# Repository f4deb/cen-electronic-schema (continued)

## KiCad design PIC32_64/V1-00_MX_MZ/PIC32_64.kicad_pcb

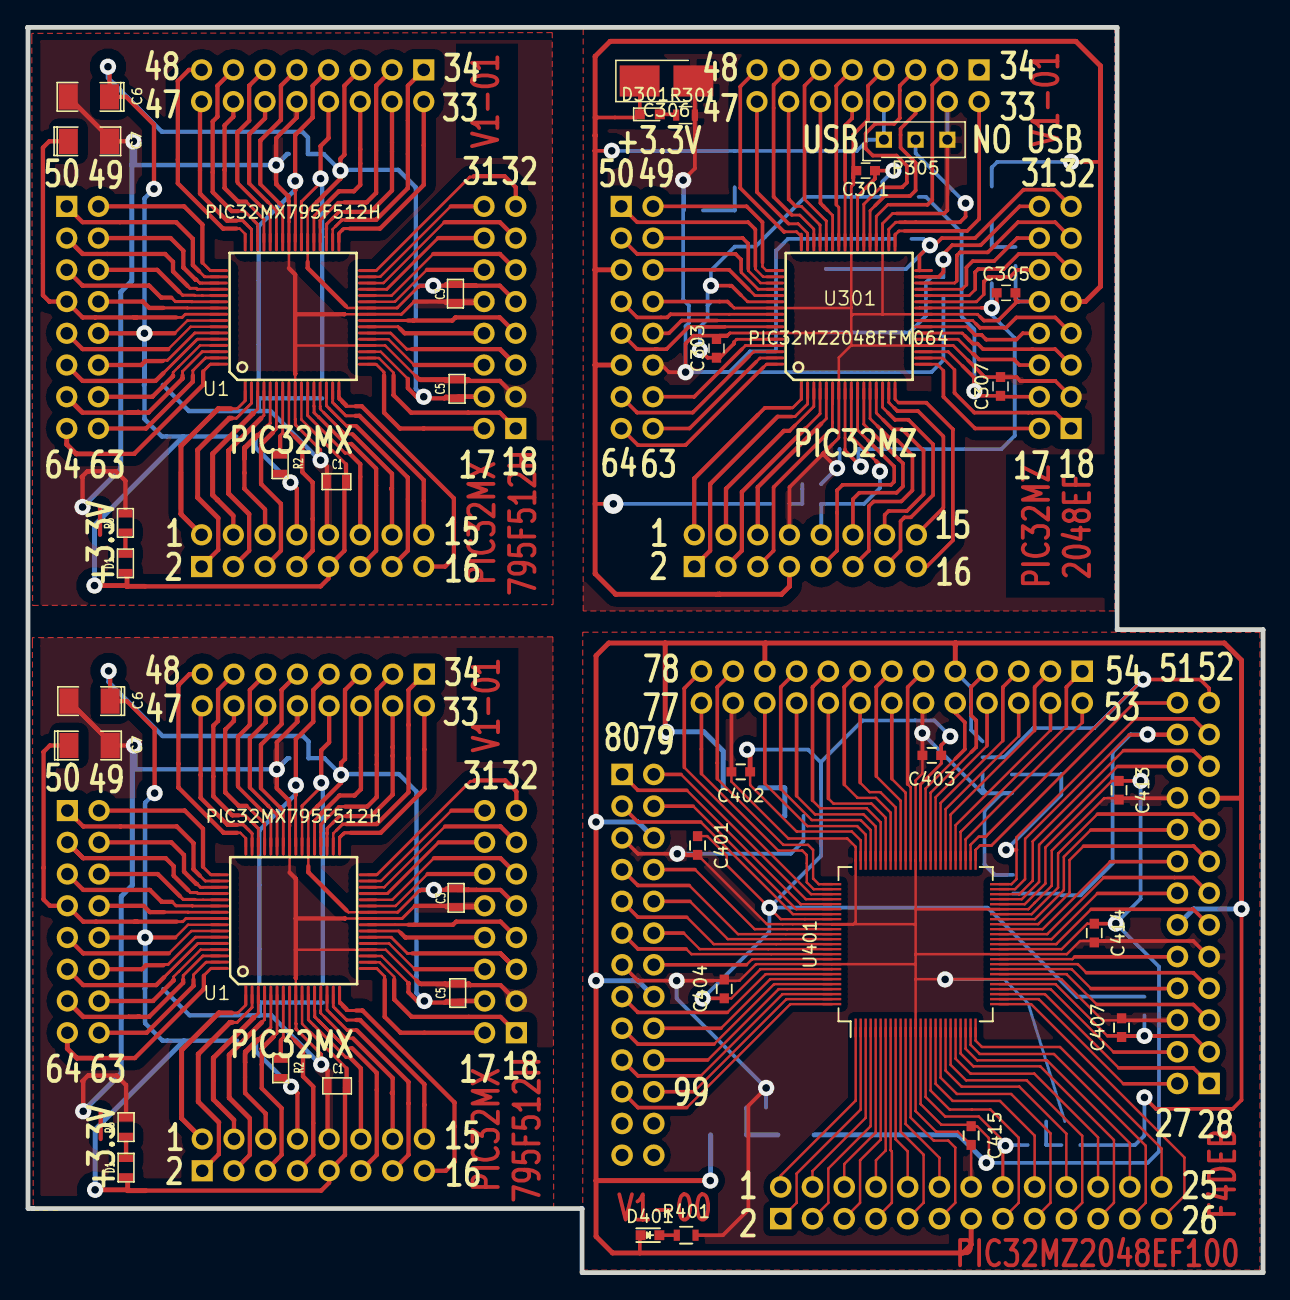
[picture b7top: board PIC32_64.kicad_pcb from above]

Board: 2 copper layers, 98.9 x 99.7 mm, 97 parts (0 on the bottom side), 213 nets.

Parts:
C1, C1#2, C2, C2#2, C3, C3#2, C4, C4#2, C5, C5#2, C8, C8#2, C9, C9#2: 100n; SM0603_Capa
C6, C6#2, C7, C7#2: 10u/10V; SM1206POL
C301, C302, C303, C304, C305, C307, C310, C401, C402, C403, C404, C407, C411, C413, C414, C415: 100n; C_0603
C306: 10u/10V; CP_Tantalum_Case-B_EIA-3528-21_Hand
C308, C309, C408, C409: 10n; C_0603
C311, C312, C410, C412: 22p; C_0603
D1, D1#2: LED; SM0603
D301, D401: LED; LED_0603
L301, L302, L303, L304, L401, L402, L403, L404: Ferrite_Bead_Small; R_1206
P1, P1#2, P2, P2#2, P3, P3#2, P4, P4#2, P301, P302, P303, P304: CONN_8X2; Socket_Strip_Straight_2x08_Pitch2.54mm
P305: CAVALIER2; SL-103-X-XX_1x03
P401, P402, P404, P405: CONN_13X2; Socket_Strip_Straight_2x13
P403: CAVALIER2; GS3
R1, R1#2: 10k; SM0603_Resistor
R2, R2#2: 470; SM0603_Resistor
R3, R3#2: 1k; SM0603_Resistor
R4, R4#2: 0; SM0603_Resistor
R301, R303, R401, R403: 1k; R_0603
R302: 0; R_1206
R304, R404: 10k; R_0603
R402: 0; R_0603
U1, U1#2: PIC32MX795F512H; TQFP_64
U301: PIC32MZ2048EFM064; TQFP_64
U401: PIC32MZ2048EF100; TQFP-100_12x12mm_Pitch0.4mm
X1, X1#2: 8Mhz; QTZ
X301: 24Mhz; QTZ
X401: 24Mhz; Crystal_HC49-SD_SMD

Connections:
+3.3V: C1.1, C1#2.1, C2.1, C2#2.1, C3.1, C3#2.1, C4.1, C4#2.1, C6.1, C6#2.1, D1.1, D1#2.1, P1.9, P1#2.9, P2.5, P2#2.5, P3.9, P3#2.9, P4.10, P4#2.10, R1.2, R1#2.2, R4.1, R4#2.1, U1.10, U1.26, U1.38, U1.57, U1#2.10, U1#2.26, U1#2.38, U1#2.57
+3.3VA: D401.1, L401.1, L403.1, P401.13, P402.12, P402.19, P403.1, P404.9, P404.21, P405.6, P405.16, R404.2
+3.3VP: C306.1, D301.1, L301.1, L303.1, P301.7, P302.9, P303.8, P304.5, P304.11, P305.1, R304.2
/1: P1.2, P1#2.2, U1.1, U1#2.1
/2: P1.1, P1#2.1, U1.2, U1#2.2
/3: P1.4, P1#2.4, U1.3, U1#2.3
/4: P1.3, P1#2.3, U1.4, U1#2.4
/5: P1.6, P1#2.6, U1.5, U1#2.5
/6: P1.5, P1#2.5, U1.6, U1#2.6
/7: P1.8, P1#2.8, R1.1, R1#2.1, R2.2, R2#2.2
/8: P1.7, P1#2.7, U1.8, U1#2.8
/11: P1.12, P1#2.12, U1.11, U1#2.11
/12: P1.11, P1#2.11, U1.12, U1#2.12
/13: P1.14, P1#2.14, U1.13, U1#2.13
/14: P1.13, P1#2.13, U1.14, U1#2.14
/15: P1.16, P1#2.16, U1.15, U1#2.15
/16: P1.15, P1#2.15, U1.16, U1#2.16
/17: P3.2, P3#2.2, U1.17, U1#2.17
/18: P3.1, P3#2.1, U1.18, U1#2.18
/19: C5.1, C5#2.1, P3.4, P3#2.4, R4.2, R4#2.2, U1.19, U1#2.19
/21: P3.6, P3#2.6, U1.21, U1#2.21
/22: P3.5, P3#2.5, U1.22, U1#2.22
/23: P3.8, P3#2.8, U1.23, U1#2.23
/24: P3.7, P3#2.7, U1.24, U1#2.24
/27: P3.12, P3#2.12, U1.27, U1#2.27
/28: P3.11, P3#2.11, U1.28, U1#2.28
/29: P3.14, P3#2.14, U1.29, U1#2.29
/30: P3.13, P3#2.13, U1.30, U1#2.30
/31: P3.16, P3#2.16, U1.31, U1#2.31
/32: P3.15, P3#2.15, U1.32, U1#2.32
/33: P2.2, P2#2.2, U1.33, U1#2.33
/34: P2.1, P2#2.1, U1.34, U1#2.34
/35: P2.4, P2#2.4, U1.35, U1#2.35
/36: P2.3, P2#2.3, U1.36, U1#2.36
/37: P2.6, P2#2.6, U1.37, U1#2.37
/39: C8.1, C8#2.1, P2.8, P2#2.8, U1.39, U1#2.39, X1.2, X1#2.2
/40: C9.1, C9#2.1, P2.7, P2#2.7, U1.40, U1#2.40, X1.1, X1#2.1
/42: P2.9, P2#2.9, U1.42, U1#2.42
/43: P2.12, P2#2.12, U1.43, U1#2.43
/44: P2.11, P2#2.11, U1.44, U1#2.44
/45: P2.14, P2#2.14, U1.45, U1#2.45
/46: P2.13, P2#2.13, U1.46, U1#2.46
/47: P2.16, P2#2.16, U1.47, U1#2.47
/48: P2.15, P2#2.15, U1.48, U1#2.48
/49: P4.2, P4#2.2, U1.49, U1#2.49
/50: P4.1, P4#2.1, U1.50, U1#2.50
/51: P4.4, P4#2.4, U1.51, U1#2.51
/52: P4.3, P4#2.3, U1.52, U1#2.52
/53: P4.6, P4#2.6, U1.53, U1#2.53
/54: P4.5, P4#2.5, U1.54, U1#2.54
/55: P4.8, P4#2.8, U1.55, U1#2.55
/56: C7.1, C7#2.1, P4.7, P4#2.7, U1.56, U1#2.56
/58: P4.9, P4#2.9, U1.58, U1#2.58
/59: P4.12, P4#2.12, U1.59, U1#2.59
/60: P4.11, P4#2.11, U1.60, U1#2.60
/61: P4.14, P4#2.14, U1.61, U1#2.61
/62: P4.13, P4#2.13, U1.62, U1#2.62
/63: P4.16, P4#2.16, U1.63, U1#2.63
/64: P4.15, P4#2.15, U1.64, U1#2.64
/PIC32MZ2048EF100/1: P401.2, U401.1
/PIC32MZ2048EF100/2: P401.1, U401.2
/PIC32MZ2048EF100/3: P401.4, U401.3
/PIC32MZ2048EF100/4: P401.3, U401.4
/PIC32MZ2048EF100/5: P401.6, U401.5
/PIC32MZ2048EF100/6: P401.5, U401.6
/PIC32MZ2048EF100/7: P401.8, U401.7
/PIC32MZ2048EF100/8: P401.7, U401.8
/PIC32MZ2048EF100/9: P401.10, U401.9
/PIC32MZ2048EF100/10: P401.9, U401.10
/PIC32MZ2048EF100/11: P401.12, U401.11
/PIC32MZ2048EF100/12: P401.11, U401.12
/PIC32MZ2048EF100/15: P401.16, R403.1, U401.15
/PIC32MZ2048EF100/16: P401.15, U401.16
/PIC32MZ2048EF100/17: P401.18, U401.17
/PIC32MZ2048EF100/18: P401.17, U401.18
/PIC32MZ2048EF100/19: P401.20, U401.19
/PIC32MZ2048EF100/20: P401.19, U401.20
/PIC32MZ2048EF100/21: P401.22, U401.21
/PIC32MZ2048EF100/22: P401.21, U401.22
/PIC32MZ2048EF100/23: P401.24, U401.23
/PIC32MZ2048EF100/24: P401.23, U401.24
/PIC32MZ2048EF100/25: P401.26, U401.25
/PIC32MZ2048EF100/26: P401.25, U401.26
/PIC32MZ2048EF100/27: P402.2, U401.27
/PIC32MZ2048EF100/28: P402.1, U401.28
/PIC32MZ2048EF100/29: P402.4, U401.29
/PIC32MZ2048EF100/30: C407.1, P402.3, R402.2, U401.30
/PIC32MZ2048EF100/32: P402.5, U401.32
/PIC32MZ2048EF100/33: P402.8, U401.33
/PIC32MZ2048EF100/34: P402.7, U401.34
/PIC32MZ2048EF100/35: P402.10, U401.35
/PIC32MZ2048EF100/38: P402.11, U401.38
/PIC32MZ2048EF100/39: P402.14, U401.39
/PIC32MZ2048EF100/40: P402.13, U401.40
/PIC32MZ2048EF100/41: P402.16, U401.41
/PIC32MZ2048EF100/42: P402.15, U401.42
/PIC32MZ2048EF100/43: P402.18, U401.43
/PIC32MZ2048EF100/44: P402.17, U401.44
/PIC32MZ2048EF100/47: P402.22, U401.47
/PIC32MZ2048EF100/48: P402.21, U401.48
/PIC32MZ2048EF100/49: C410.1, P402.24, U401.49, X401.2
/PIC32MZ2048EF100/50: C412.1, P402.23, U401.50, X401.1
/PIC32MZ2048EF100/51: P402.26, U401.51
/PIC32MZ2048EF100/52: P402.25, P403.2, U401.52
/PIC32MZ2048EF100/53: P404.2, U401.53
/PIC32MZ2048EF100/54: P404.1, U401.54
/PIC32MZ2048EF100/55: P404.4, U401.55
/PIC32MZ2048EF100/56: P404.3, U401.56
/PIC32MZ2048EF100/57: P404.6, U401.57
/PIC32MZ2048EF100/58: P404.5, U401.58
/PIC32MZ2048EF100/59: P404.8, U401.59
/PIC32MZ2048EF100/60: P404.7, U401.60
/PIC32MZ2048EF100/61: P404.10, U401.61
/PIC32MZ2048EF100/64: P404.11, U401.64
/PIC32MZ2048EF100/65: P404.14, U401.65
/PIC32MZ2048EF100/66: P404.13, U401.66
/PIC32MZ2048EF100/67: P404.16, U401.67
/PIC32MZ2048EF100/68: P404.15, U401.68
/PIC32MZ2048EF100/69: P404.18, U401.69
/PIC32MZ2048EF100/70: P404.17, U401.70
/PIC32MZ2048EF100/71: P404.20, U401.71
/PIC32MZ2048EF100/72: P404.19, U401.72
/PIC32MZ2048EF100/73: P404.22, U401.73
/PIC32MZ2048EF100/76: P404.23, U401.76
/PIC32MZ2048EF100/77: P404.26, U401.77
/PIC32MZ2048EF100/78: P404.25, U401.78
/PIC32MZ2048EF100/79: P405.2, U401.79
/PIC32MZ2048EF100/80: P405.1, U401.80
/PIC32MZ2048EF100/81: P405.4, U401.81
/PIC32MZ2048EF100/82: P405.3, U401.82
/PIC32MZ2048EF100/85: P405.8, U401.85
/PIC32MZ2048EF100/86: P405.7, U401.86
/PIC32MZ2048EF100/87: P405.10, U401.87
/PIC32MZ2048EF100/88: P405.9, U401.88
/PIC32MZ2048EF100/89: P405.12, U401.89
/PIC32MZ2048EF100/90: P405.11, U401.90
/PIC32MZ2048EF100/91: P405.14, U401.91
/PIC32MZ2048EF100/94: P405.15, U401.94
/PIC32MZ2048EF100/95: P405.18, U401.95
/PIC32MZ2048EF100/96: P405.17, U401.96
/PIC32MZ2048EF100/97: P405.20, U401.97
/PIC32MZ2048EF100/98: P405.19, U401.98
/PIC32MZ2048EF100/99: P405.22, U401.99
/PIC32MZ2048EF100/100: P405.21, U401.100
/PIC32MZ20048EF64/1: P301.2, U301.1
/PIC32MZ20048EF64/2: P301.1, U301.2
/PIC32MZ20048EF64/3: P301.4, U301.3
/PIC32MZ20048EF64/4: P301.3, U301.4
/PIC32MZ20048EF64/5: P301.6, U301.5
/PIC32MZ20048EF64/6: P301.5, U301.6
/PIC32MZ20048EF64/9: P301.10, R303.1, U301.9
/PIC32MZ20048EF64/10: P301.9, U301.10
/PIC32MZ20048EF64/11: P301.12, U301.11
/PIC32MZ20048EF64/12: P301.11, U301.12
/PIC32MZ20048EF64/13: P301.14, U301.13
/PIC32MZ20048EF64/14: P301.13, U301.14
/PIC32MZ20048EF64/15: P301.16, U301.15
/PIC32MZ20048EF64/16: P301.15, U301.16
/PIC32MZ20048EF64/17: P302.2, U301.17
/PIC32MZ20048EF64/18: P302.1, U301.18
/PIC32MZ20048EF64/19: C307.1, P302.4, R302.2, U301.19
/PIC32MZ20048EF64/21: P302.6, U301.21
/PIC32MZ20048EF64/22: P302.5, U301.22
/PIC32MZ20048EF64/23: P302.8, U301.23
/PIC32MZ20048EF64/24: P302.7, U301.24
/PIC32MZ20048EF64/27: P302.12, U301.27
/PIC32MZ20048EF64/28: P302.11, U301.28
/PIC32MZ20048EF64/29: P302.14, U301.29
/PIC32MZ20048EF64/30: P302.13, U301.30
/PIC32MZ20048EF64/31: C312.1, P302.16, U301.31, X301.1
/PIC32MZ20048EF64/32: C311.1, P302.15, U301.32, X301.2
/PIC32MZ20048EF64/33: P303.2, U301.33
/PIC32MZ20048EF64/36: P303.3, U301.36
/PIC32MZ20048EF64/37: P303.6, U301.37
/PIC32MZ20048EF64/38: P303.5, U301.38
/PIC32MZ20048EF64/41: P303.10, U301.41
/PIC32MZ20048EF64/42: P303.9, U301.42
/PIC32MZ20048EF64/43: P303.12, U301.43
/PIC32MZ20048EF64/44: P303.11, U301.44
/PIC32MZ20048EF64/45: P303.14, U301.45
/PIC32MZ20048EF64/46: P303.13, U301.46
/PIC32MZ20048EF64/47: P303.16, U301.47
/PIC32MZ20048EF64/48: P303.15, U301.48
/PIC32MZ20048EF64/49: P304.2, U301.49
/PIC32MZ20048EF64/50: P304.1, U301.50
/PIC32MZ20048EF64/51: P304.4, U301.51
/PIC32MZ20048EF64/52: P304.3, U301.52
/PIC32MZ20048EF64/53: P304.6, U301.53
/PIC32MZ20048EF64/56: P304.7, U301.56
/PIC32MZ20048EF64/57: P304.10, U301.57
/PIC32MZ20048EF64/58: P304.9, U301.58
/PIC32MZ20048EF64/61: P304.14, U301.61
/PIC32MZ20048EF64/62: P304.13, U301.62
/PIC32MZ20048EF64/63: P304.16, U301.63
/PIC32MZ20048EF64/64: P304.15, U301.64
GND: C1.2, C1#2.2, C2.2, C2#2.2, C3.2, C3#2.2, C4.2, C4#2.2, C5.2, C5#2.2, C6.2, C6#2.2, C7.2, C7#2.2, C8.2, C8#2.2, C9.2, C9#2.2, P1.10, P1#2.10, P2.10, P2#2.10, P3.3, P3.10, P3#2.3, P3#2.10, R3.2, R3#2.2, U1.9, U1.20, U1.25, U1.41, U1#2.9, U1#2.20, U1#2.25, U1#2.41
GNDA: C401.2, C402.2, C403.2, C404.2, C407.2, C408.2, C409.2, C410.2, C411.2, C412.2, C413.2, C414.2, C415.2, P401.14, P402.6, P402.9, P402.20, P403.3, P404.12, P404.24, P405.5, P405.13, R401.2, U401.13, U401.31, U401.36, U401.45, U401.63, U401.75, U401.84, U401.92
GNDD: C301.2, C302.2, C303.2, C304.2, C305.2, C306.2, C307.2, C308.2, C309.2, C310.2, C311.2, C312.2, P301.8, P302.3, P302.10, P303.4, P303.7, P304.8, P304.12, P305.3, R301.2, U301.7, U301.20, U301.25, U301.35, U301.40, U301.55, U301.59
unnamed: R2.1, R2#2.1, U1.7, U1#2.7
unnamed: D1.2, D1#2.2, R3.1, R3#2.1
unnamed: C301.1, C302.1, C303.1, L302.2, R302.1, U301.39, U301.54, U301.60
unnamed: C304.1, C305.1, L304.2, U301.8, U301.26
unnamed: C308.1, L301.2, L302.1
unnamed: C309.1, L303.2, L304.1
unnamed: C310.1, R303.2, R304.1
unnamed: C401.1, C402.1, C403.1, C404.1, L402.2, R402.1, U401.62, U401.74, U401.83, U401.93
unnamed: C408.1, L401.2, L402.1
unnamed: C409.1, L403.2, L404.1
unnamed: C411.1, R403.2, R404.1
unnamed: C413.1, C414.1, C415.1, L404.2, U401.14, U401.37, U401.46
unnamed: D301.2, R301.1
unnamed: D401.2, R401.1
unnamed: P305.2, U301.34

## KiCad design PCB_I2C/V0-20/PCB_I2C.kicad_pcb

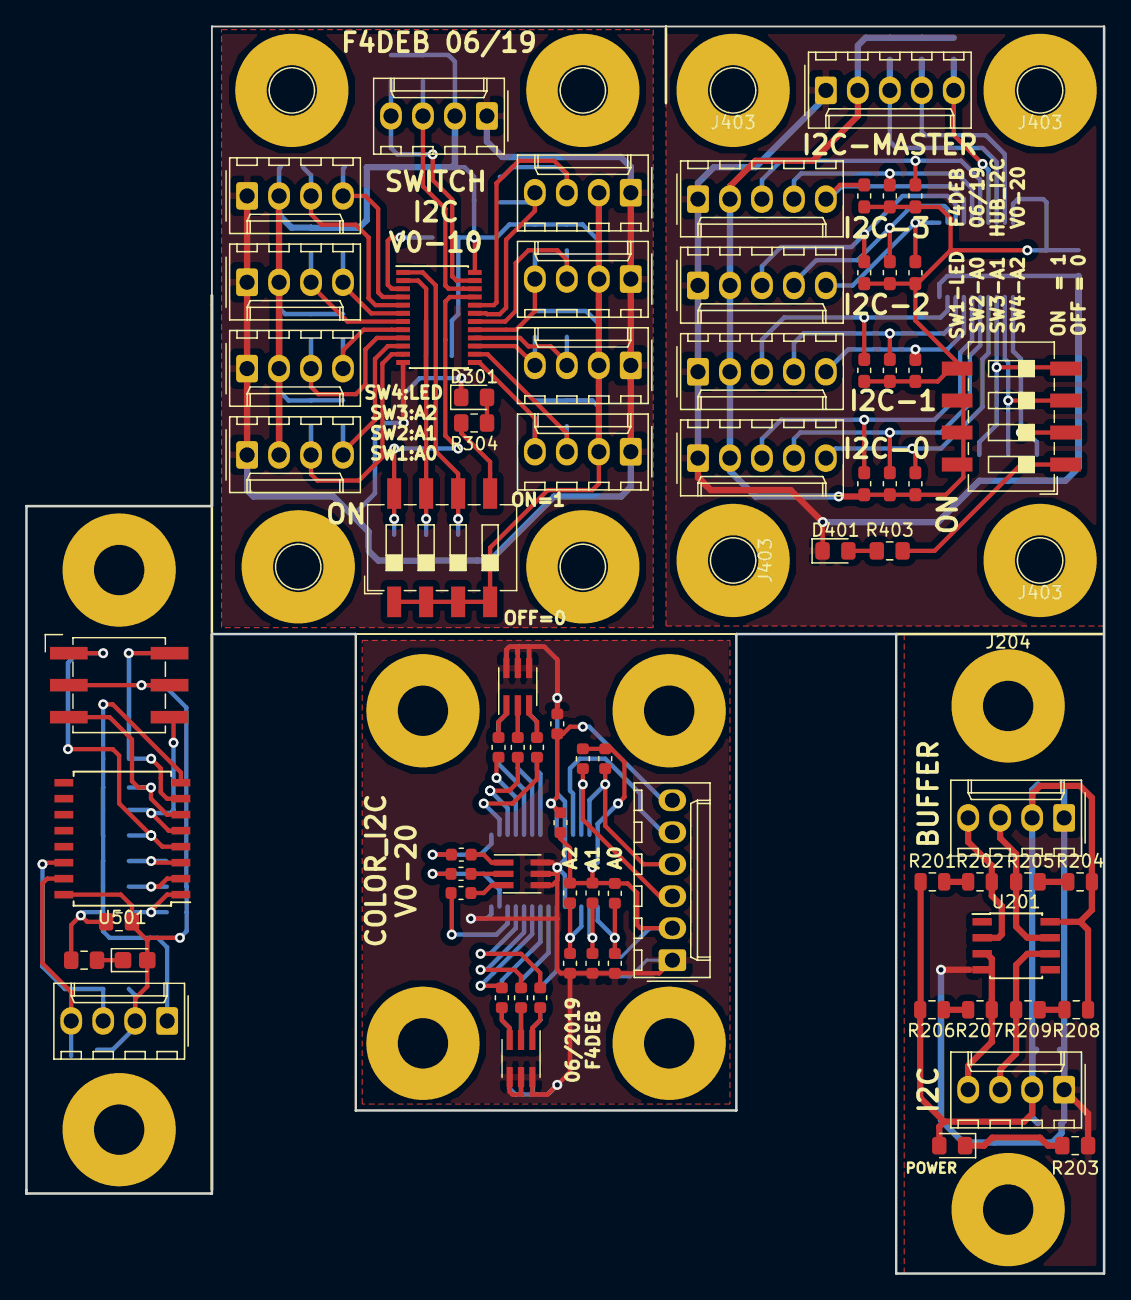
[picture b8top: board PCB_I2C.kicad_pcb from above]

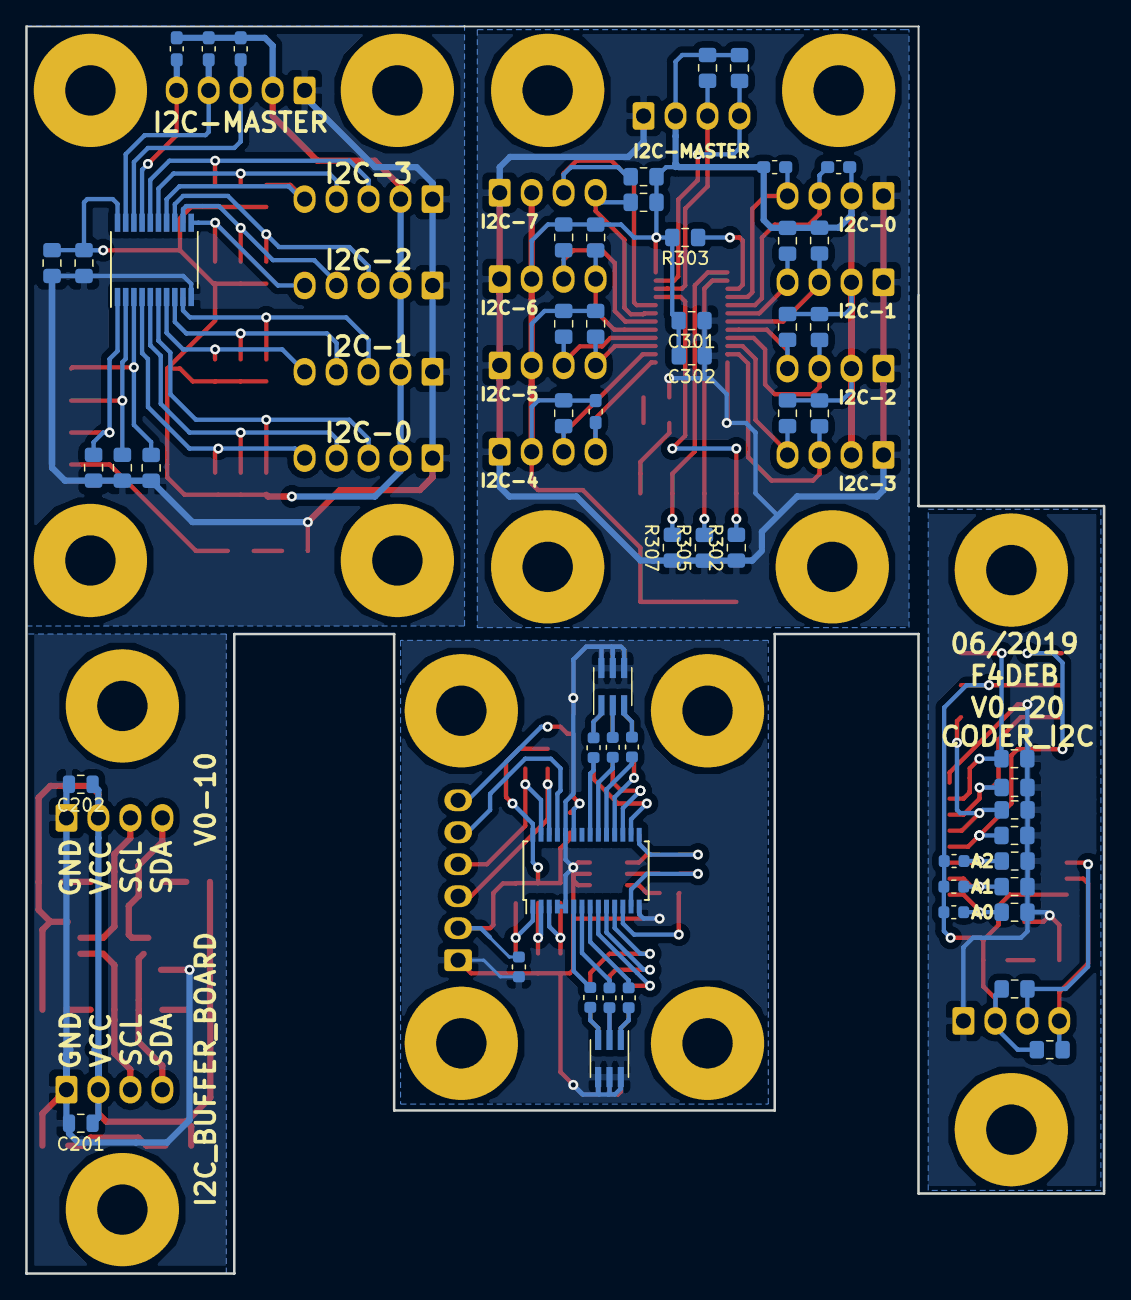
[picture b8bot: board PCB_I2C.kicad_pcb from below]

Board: 2 copper layers, 85.6 x 99.1 mm, 148 parts (57 on the bottom side), 110 nets.

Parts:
C201: 1u; C_0805_2012Metric
C202: 100n; C_0805_2012Metric
C301, C501: 100n; C_0805_2012Metric_Pad1.15x1.40mm_HandSolder
C302: 1u; C_0805_2012Metric_Pad1.15x1.40mm_HandSolder
C401, C402: C; C_0805_2012Metric_Pad1.15x1.40mm_HandSolder
C601: 100n; C_0603_1608Metric
D201: LED Vert; LED_0805_2012Metric_Pad1.15x1.40mm_HandSolder
D301, D401: VERT; LED_0805_2012Metric_Pad1.15x1.40mm_HandSolder
D501: VERT; D_0805_2012Metric_Castellated
D601, D602, D603, D604, D605: ASMT-YTB7-0AA02; LED_Avago_PLCC6_3x2.8mm
J201, J202, J301, J302, J305, J306, J307, J308, J309, J310, J311: Conn_01x04_Male; Molex_KK-254_AE-6410-04A_1x04_P2.54mm_Vertical
J203, J204, J502, J502#2, J502#3, J502#4, J502#5, J503: Conn_01x01_Female; SolderWirePad_1x01_Drill2.5mm
J303, J303#2, J304, J304#2, J403, J403#2, J403#3, J403#4: Conn_01x01_Female; Pin_D1.3mm_L11.0mm_LooseFit
J401, J404, J405, J406, J407: Conn_01x05_Male; Molex_KK-254_AE-6410-05A_1x05_P2.54mm_Vertical
J501: Conn_01x04; Molex_KK-254_AE-6410-04A_1x04_P2.54mm_Vertical
J601: Conn_01x04; Molex_KK-254_AE-6410-06A_1x06_P2.54mm_Vertical
R201, R204, R206, R208: 0; R_0805_2012Metric
R202, R205, R207, R209: 2k1; R_0805_2012Metric
R203, R304, R403, R501: 1k; R_0805_2012Metric_Pad1.15x1.40mm_HandSolder
R301, R306, R310, R311, R312, R313, R314, R315, R316, R318, R319, R320, R321, R322, R323: 2.1k; R_0805_2012Metric_Pad1.15x1.40mm_HandSolder
R302, R305, R307, R402, R405, R406, R502, R504, R506, R507, R509, R511, R513: 47k; R_0805_2012Metric_Pad1.15x1.40mm_HandSolder
R303, R503, R505: 10k; R_0805_2012Metric_Pad1.15x1.40mm_HandSolder
R308, R309, R317: 2.1k; R_0603_1608Metric_Pad1.05x0.95mm_HandSolder
R401, R404, R407, R408, R411, R414, R417: 10k; R_0603_1608Metric_Pad1.05x0.95mm_HandSolder
R409, R410, R412, R413, R415, R416, R418, R419: 4k7; R_0603_1608Metric_Pad1.05x0.95mm_HandSolder
R515, R516, R517, R626, R627, R628: 0; R_0603_1608Metric
R603, R604, R607, R609: 10k; R_0603_1608Metric
R606, R608, R610: 47k; R_0603_1608Metric
R611, R612, R613, R614, R615, R616, R617, R618, R619, R620, R621, R622, R623, R624, R625: R; R_0603_1608Metric
SW301, SW401: SW_DIP_x04; SW_DIP_SPSTx04_Slide_6.7x11.72mm_W8.61mm_P2.54mm_LowProfile
SW502: SW_Coded_SH-7050; Nidec_Copal_SH-7010B
U201: P82B715; SOIC-8_3.9x4.9mm_P1.27mm
U301: TCA9548APWR; TSSOP-24_4.4x7.8mm_P0.65mm
U401: TCA9544A; TSSOP-20_4.4x6.5mm_P0.65mm
U501: PCF8574A; SOIC-16W_7.5x10.3mm_P1.27mm
U601: PCA9685PW; TSSOP-28_4.4x9.7mm_P0.65mm

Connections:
/RGB/B0: R619.2, U601.11
/RGB/B1: R611.2, U601.21
/RGB/B2: R617.2, U601.18
/RGB/B3: R612.2, U601.8
/RGB/B4: R618.2, U601.15
/RGB/R0: R625.2, U601.9
/RGB/R1: R615.2, U601.19
/RGB/R2: R623.2, U601.16
/RGB/R3: R616.2, U601.6
/RGB/R4: R624.2, U601.12
/RGB/V0: R622.2, U601.10
/RGB/V1: R613.2, U601.20
/RGB/V2: R620.2, U601.17
/RGB/V3: R614.2, U601.7
/RGB/V4: R621.2, U601.13
unnamed: C201.1, C202.1, D201.2, J201.2, J202.2, R201.1, R204.1, R206.1, R208.1, U201.8
unnamed: C201.2, C202.2, J201.1, J202.1, R203.2, U201.4
unnamed: C301.1, C302.1, D301.1, J301.1, J302.1, J305.1, J306.1, J307.1, J308.1, J309.1, J310.1, J311.1, R302.1, R305.1, R307.1, U301.12
unnamed: C301.2, C302.2, J301.2, J302.2, J305.2, J306.2, J307.2, J308.2, J309.2, J310.2, J311.2, R301.1, R303.2, R306.1, R308.1, R309.1, R310.1, R311.1, R312.1, R313.1, R314.1, R315.1, R316.1, R317.1, R318.1, R319.1, R320.1, R321.1, R322.1, R323.1, SW301.1, SW301.2, SW301.3, SW301.4, U301.24
unnamed: C401.1, C402.1, D401.1, J401.1, J404.1, J405.1, J406.1, J407.1, R402.1, R405.1, R406.1, U401.10
unnamed: C401.2, C402.2, J401.2, J404.2, J405.2, J406.2, J407.2, R401.1, R404.1, R407.1, R408.1, R409.1, R410.1, R411.1, R412.1, R413.1, R414.1, R415.1, R416.1, R417.1, R418.1, R419.1, SW401.5, SW401.6, SW401.7, SW401.8, U401.20
unnamed: C501.1, D501.2, J501.2, R503.1, R505.1, R515.2, R516.2, R517.2, SW502.C, U501.16
unnamed: C501.2, J501.1, R501.1, R502.2, R504.2, R506.2, R507.2, R509.2, R511.2, R513.2, U501.8
unnamed: C601.1, J601.2, R603.1, R607.1, R609.1, R626.2, R627.2, R628.2, U601.28
unnamed: C601.2, D601.4, D601.5, D601.6, D602.4, D602.5, D602.6, D603.4, D603.5, D603.6, D604.4, D604.5, D604.6, D605.4, D605.5, D605.6, J601.1, R604.2, R606.2, R608.2, R610.2, U601.4, U601.5, U601.14, U601.24
unnamed: D201.1, R203.1
unnamed: D301.2, R304.1
unnamed: D401.2, R403.1
unnamed: D501.1, R501.2
unnamed: D601.1, R611.1
unnamed: D601.2, R613.1
unnamed: D601.3, R615.1
unnamed: D602.1, R612.1
unnamed: D602.2, R614.1
unnamed: D602.3, R616.1
unnamed: D603.1, R617.1
unnamed: D603.2, R620.1
unnamed: D603.3, R623.1
unnamed: D604.1, R618.1
unnamed: D604.2, R621.1
unnamed: D604.3, R624.1
unnamed: D605.1, R619.1
unnamed: D605.2, R622.1
unnamed: D605.3, R625.1
unnamed: J201.3, R205.2, U201.7
unnamed: J201.4, R202.2, U201.2
unnamed: J202.3, R209.2, U201.6
unnamed: J202.4, R207.2, U201.3
unnamed: J301.3, R301.2, U301.22
unnamed: J301.4, R306.2, U301.23
unnamed: J302.3, R308.2, U301.5
unnamed: J302.4, R309.2, U301.4
unnamed: J305.3, R310.2, U301.7
unnamed: J305.4, R311.2, U301.6
unnamed: J306.3, R312.2, U301.9
unnamed: J306.4, R313.2, U301.8
unnamed: J307.3, R314.2, U301.11
unnamed: J307.4, R315.2, U301.10
unnamed: J308.3, R316.2, U301.14
unnamed: J308.4, R317.2, U301.13
unnamed: J309.3, R318.2, U301.16
unnamed: J309.4, R319.2, U301.15
unnamed: J310.3, R320.2, U301.18
unnamed: J310.4, R321.2, U301.17
unnamed: J311.3, R322.2, U301.20
unnamed: J311.4, R323.2, U301.19
unnamed: J401.3, R401.2, U401.18
unnamed: J401.4, R404.2, U401.19
unnamed: J401.5, R407.2, U401.17
unnamed: J404.3, R409.2, U401.6
unnamed: J404.4, R410.2, U401.5
unnamed: J404.5, R408.2, U401.4
unnamed: J405.3, R412.2, U401.9
unnamed: J405.4, R413.2, U401.8
unnamed: J405.5, R411.2, U401.7
unnamed: J406.3, R415.2, U401.13
unnamed: J406.4, R416.2, U401.12
unnamed: J406.5, R414.2, U401.11
unnamed: J407.3, R418.2, U401.16
unnamed: J407.4, R419.2, U401.15
unnamed: J407.5, R417.2, U401.14
unnamed: J501.3, R503.2, U501.14
unnamed: J501.4, R505.2, U501.15
unnamed: J601.3, R607.2, U601.26
unnamed: J601.4, R609.2, U601.27
unnamed: J601.5, U601.25
unnamed: J601.6, R603.2, R604.1, U601.23
unnamed: R201.2, R202.1
unnamed: R204.2, R205.1
unnamed: R206.2, R207.1
unnamed: R208.2, R209.1
unnamed: R302.2, SW301.8, U301.21
unnamed: R303.1, U301.3
unnamed: R304.2, SW301.5
unnamed: R305.2, SW301.7, U301.2
unnamed: R307.2, SW301.6, U301.1
unnamed: R402.2, SW401.4, U401.3
unnamed: R403.2, SW401.1
unnamed: R405.2, SW401.3, U401.2
unnamed: R406.2, SW401.2, U401.1
unnamed: R502.1, R517.1, U501.3
unnamed: R504.1, R516.1, U501.2
unnamed: R506.1, R515.1, U501.1
unnamed: R507.1, SW502.8, U501.7
unnamed: R509.1, SW502.4, U501.6
unnamed: R511.1, SW502.2, U501.5
unnamed: R513.1, SW502.1, U501.4
unnamed: R606.1, R628.1, U601.3
unnamed: R608.1, R627.1, U601.2
unnamed: R610.1, R626.1, U601.1

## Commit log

2012-06-03 Issue 1 : Schema of PIC32_64
2012-06-04 Ajout empreinte PIC32_64
2012-06-04 Modif Schema
2012-06-08 Routage 66%
2012-06-09 SCHEMA 100% PCB 100%
2012-06-09 ajout sch PIC32_64
2012-06-09 en vrac
2012-06-09 modif empreinte PCA9306 modif pistes diverses
2012-06-10 SCHEMA + PCB 100% ELECTRONICAL_MAIN_BOARD_32 V0-10 PIC32_64 V1-00 GRAVER LE 6-10-2012
2012-06-13 Ajout valeurs composants
2012-07-22 ELECTRONICAL_MAIN_BOARD_32
2012-07-23 mise a jour PCB 1-10
2012-08-16 pb git ok
2012-08-26 modif valeur composant
2012-08-26 deplacement de la librairie
2012-08-26 mise a jour mineur
2012-08-27 Ajout SCHEMA JN5139
2012-08-29 mise a jour valeur
2012-09-05 nouvelle version pour corriger le défaut de bus pour le LCD
2012-09-11 mise a jour v1-20
2012-09-18 V1-20 electronical_main_board MAJ
2012-09-24 V1-20 Electronical_MAIN_BOARD_32
2012-10-09 MAJ V1-30
2013-01-12 RARAS
2013-03-23 RECHERCHE NOUVELLE CARTE JN5139
2013-04-06 MAJ MOTOR BOARD PIC32 ADPTATION NIVEAU
2013-04-21 Routage Motor Board Pic32 + DSPIC ok
2013-04-27 test
2013-04-27 Ajout carte DSPIC_40
2013-04-28 MAJ Kicad nouvelle version
2013-05-20 MAJ 3D
2013-08-03 MAJ min
2013-08-19 MOTOR BOARD V3-00
2013-08-27 MAJ MINEUR
2013-08-27 AJOUT DSPIC_40
2013-08-31 MAJ pour impression
2013-12-09 recup des anciennes versions electronical main board
2014-05-20 UPDATE JJ AVEC MOTOR BOARD 32 BITS
2014-05-30 Creation Motor Board 32 V3-20
2014-06-01 MAJ PCB V3-20 READY FOR PRODUTION
2014-07-02 nettoyage motor_board repo
2014-07-02 REPO SCHEMA CLEANED
2014-07-11 IOIO_BOARD SCHEMA 80%
2014-07-13 Schema 100% Routage 50%
2014-07-14 PCB 90%
2014-07-15 PIN NAME ADJUST TO BE SAME AS THE ORIGINAL
2014-07-16 MAJ PCB via ->1,3 + empreinte .L1117
2014-07-17 ADD EEPROM_I2C BOARD 100%
2014-07-18 CREATE RTC_I2C READY FOR PRODUCTION
2014-07-19 ADD 3D VISU
2014-07-20 Modification for printing
2014-09-29 ADD LM75ADP
2014-11-05 ELECTRONICAL MAIN BOARD V1-30 Ready for production
2015-01-10 ELECTRONICAL_MAIN_BOARD_32 V1-30 + Motor Board V3-30
2015-01-11 MOTOR_BOARD V3.3 V3.4
2015-03-13 Motor_Board_32 V3-41
2015-05-14 ADD USB TO UART V0-10
2015-07-15 MAJ USB TO 4UART + ADD NEW MECHANICAL BOARD
2015-07-27 ADD MECHANICAL MAIN BOARD V0-10
2015-08-02 MAJ mechanical Main board CPU1
2015-08-02 ADD 3D BOARD for solideworks test
2015-08-06 MECHANICAL MOTOR BOARD
2015-08-20 MAJ mechanical_motor_board
2015-10-10 mechanical motor board v0.1+ mechanical main board v1.0
2015-10-10 Mechanical Power Board V1-00 ready for production
2015-10-20 test mechanicalmotorboard PCB NOK
2015-12-06 New Beacon_Main_Board
2015-12-06 MAJ wiki img
2015-12-08 MAJ BEACON_MAIN_BOARD
2015-12-15 Beacon_Main_Board 50%
2015-12-16 PCB 80%
2016-05-14 ELECTRONICAL_MAIN_BOARD_32 V1-40
2016-05-15 MAJ ELECTRONICAL_MAIN_BOARD_32 V1_40
2016-05-24 MAJ Q5 IRFL9114
2017-03-22 MAJ??
2017-07-10 MAJ ICD BOARD + 3D Mechanical Power Board V0.10
2017-11-19 MAJ CONNECTORS_BOARD V0-20
2018-02-27 MAJ 2018
2018-10-26 MAJ 09/2018
2018-12-05 ICHUB/PCF8574
2019-02-16 Mechanical power board V2-00
2019-02-26 CONNECTOR BOARD V2-00
2019-02-27 Add Silk Screen
2019-03-02 Add IOEXPANDER TEST
2019-03-08 MAJ Mechanical_Power_Board
2019-06-30 COMMANDE PCB_I2C
2019-07-30 Add IO_8_BUTTON_BOARD to the repository
2019-07-30 Change Led footprints from 0603 to 0805
2019-10-29 MAJ HALF DUPLEX
2020-01-05 MOTOR_BOARD_I2C ADD
2020-01-23 RGB_PCA9685
2020-03-25 prog test RGB
2020-03-25 CODER_LEVEL_BOARD Begin
2020-03-27 CODER LEVEL UPDATE Ready to Product
2020-04-23 add mother_board
2020-04-23 add img
2020-04-23 JST PH
2020-04-25 doc color_I2C
2020-06-17 PIC32MZ
2020-06-18 MAJ MOTHER BOARD
2020-06-27 MAJ mother_board
2020-07-18 Mother Board update
